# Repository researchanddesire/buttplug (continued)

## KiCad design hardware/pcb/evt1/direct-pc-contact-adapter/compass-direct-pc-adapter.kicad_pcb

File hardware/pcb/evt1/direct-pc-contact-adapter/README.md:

# Compass EVT1 direct PC contact adapter

EVT1-EA1 is a 35 × 26 × 1.6 mm four-layer external bench adapter. It connects a USB-C data port to the same four plug contacts used by the dock. The plug continues to use its native USB device interface. Connect the adapter fixture or the dock to the plug, one at a time. Routine enumeration uses the plug’s existing USB firmware.

- [KiCad project](compass-direct-pc-adapter.kicad_pro)
- [Schematic](compass-direct-pc-adapter.kicad_sch)
- [Board](compass-direct-pc-adapter.kicad_pcb)
- [Gerber and drill ZIP](quote/compass-direct-pc-adapter-gerbers.zip), [BOM](quote/compass-direct-pc-adapter-bom.csv), [placement](quote/compass-direct-pc-adapter-cpl.csv), [native checks](quote/review.json)

## Connection

J1 uses the GCT USB4105-GF-A-120 from the bench board. Each CC line has its own 5.1 kΩ pull-down. Use a native USB-C data port or powered data hub rated to supply at least 500 mA at 5 V for the first evaluation. The adapter requests default 5 V using the CC resistors and has no USB PD controller. [Bench schematic source](../one-board-dev/build_schematic.py) · [GCT drawing](https://gct.co/files/drawings/usb4105.pdf)

J2 is a top-entry JST PH B4B-PH-K(LF)(SN). Mate it with a JST PHR-4 and SPH-002T-P0.5S crimp contacts rated for the selected wire. Use a short, strain-relieved harness with equal-length D− and D+ conductors. Have the harness assembler terminate the far end on the pin board’s J94 pads. The four-pin harness is a distinct assembly. The BOM covers all 25 populated positions on the adapter PCB. [JST PH series](https://www.jst-mfg.com/product/pdf/eng/ePH.pdf) · [J94 harness source](../../../cables/evt1/dock-main/main-to-pins.yml)

| J2 to J94 | Pin signal |
| --- | --- |
| 1 to 1 | GND |
| 2 to 2 | USB D− |
| 3 to 3 | USB D+ |
| 4 to 4 | Protected 5 V |

Viewed from above with the USB connector facing the front edge, J2 pin 1 is on the right. Measured from the PCB’s front-left corner, the USB-C footprint origin is (17.5, 2.675) mm and its mating face is 1.0 mm proud. J2 pin 1 is (20.5, 21) mm and pin 4 is (14.5, 21) mm. The 2.2 mm nonplated mounting holes are at (3, 3), (32, 3), (3, 23), and (32, 23) mm. Allow wire exit above J2 and clearance for both connector tails under the board.

## Power and data

U1 limits forward contact power. The 191 kΩ, 0.5% R3 yields approximately 120–166 mA DC across the published limit equations, using a conservative ±1% resistor allowance for initial tolerance and temperature drift. The plug’s BQ24074 is strapped for USB100 with a 100 mA maximum input. The plug’s 10 kΩ and 11 kΩ branch pull-ups add up to about 1 mA at 5 V if both are pulled low. Adapter logic is supplied from J1 ahead of U1. Budget 1 mA additional upstream current for the adapter on first test and measure the actual configured and suspended current. [TPS2553-Q1 current limit](https://www.ti.com/lit/ds/symlink/tps2553-q1.pdf) · [BQ24074 USB100](https://www.ti.com/lit/ds/symlink/bq24074.pdf)

U2 is wired as an ideal diode with its CE tied to its output. It blocks sustained current from J2 towards J1. U4 senses the limiter output ahead of that reverse block. The TPS3808G09DBVR uses a 41.2 kΩ/10.0 kΩ divider. The estimated LIMIT_5V trips are 4.31 V falling and 4.35 V rising, with a 12–28 ms release delay (20 ms typical) after a valid rise. U4 and the PI3USB42 switch share the adapter 3.3 V rail. The PI3USB42 uses the A pair only and is high impedance with its supply off. Ground-referenced ESD arrays sit on both sides. The inactive pair on U5 has open pads. [LM66100 reverse blocking](https://www.ti.com/lit/ds/symlink/lm66100.pdf) · [TPS3808 timing](https://www.ti.com/lit/ds/symlink/tps3808.pdf) · [TPS7A20 capacitance](https://www.ti.com/lit/ds/symlink/tps7a20.pdf) · [PI3USB42 power-off behavior](https://www.diodes.com/datasheet/download/PI3USB42.pdf)

The threshold estimate uses TI’s nominal 4 MΩ SENSE input and 0.84 V falling threshold. Across 0–60 °C, stacking resistor initial tolerance and drift, ±1.25% threshold accuracy and 2.5% maximum hysteresis gives a rising estimate of about 4.53 V with the nominal input model. As a sensitivity check, imposing 1.7 µA at the SENSE trip gives about 4.59 V with the same corners. TI specifies that current as typical at 6.5 V. Measure both thresholds on each evaluation board under load. The more conductive divider adds approximately 0.10 mA to the switched rail at 5 V. [TPS3808 electrical characteristics and input model](https://www.ti.com/lit/ds/symlink/tps3808.pdf)

The circuit senses supply validity even with no product in the fixture. Physical contact alignment and make/break order determine what happens at the mating interface. Cold mate and disconnect the USB-C cable before swapping fixtures during initial bring-up. Keep the dock and adapter physically separate.

## First article

1. Check continuity and pin order from J2 through all four contacts before applying power. With the plug absent, sweep the input with a current-limited lab source. Capture PC_5V, LIMIT_5V, CONTACT_5V, ADAPTER_3V3 and DATA_OEn. Confirm C4 provides at least 0.47 µF effective at 3.3 V, including bias and temperature. For the room-temperature evaluation, screen for a rising trip at or below 4.55 V on LIMIT_5V and verify repeatable release under the 100 mA load. Confirm that the data switch opens below the measured falling threshold and during power removal, brownout and contact-rail overload.
2. Verify at least 4.60 V at J2 under a 100 mA static electronic load with 4.75 V at J1. Sweep the limiter through onset, confirm the DC limit on the received board, and capture momentary short current and recovery. With J1 unpowered, force 5 V at J2 pin 4 against GND from a limited supply and record J1 voltage/current. Repeat the reverse-current pulse capture with both sides on protected lab supplies.
3. Measure VBUS inrush at the host connector with the fixture already mated. J1 has 3.2 µF nominal decoupling ahead of U1 and the path after U1 adds 2 µF local plus the plug’s 4.8 µF nominal charger-input bank. The regulator output, ceramic bias, soft start, contact bounce and host current limit affect the waveform. Compare charge exceeding 100 mA against the 50 µC USB 2.0 reference in TI’s charger datasheet and capture PC and plug rails. Inspect VBUS_CHG and PGOOD at the plug to detect its diode/fuse drop and any charger input regulation. [BQ24074 inrush and input DPM](https://www.ti.com/lit/ds/symlink/bq24074.pdf)
4. With a known-good protected pack, test both USB-C cable orientations, enumeration, normal update, forced ROM recovery, charge state and detach/replug. Repeat across the intended pack states, source and cable combinations before relying on depleted-pack recovery. Capture all four contact states during partial travel on the physical fixture before live swapping. A nominal PCB or dry mating study cannot establish contact order or bounce behavior.

## Quote inputs

Request standard assembly with J1 shell stakes and J2 through-hole pins assembled at the factory. Verify the USB4105 land pattern’s 0.15 mm locating-hole clearance, J1 stake solder method and J1/J2 orientation in the assembly preview. The BOM maps all 18 order lines to vendor catalog codes. The J2 placement uses the housing center from the KiCad fabrication outline. Confirm actual stock and assembly process support in the quote. The supervisor and both divider values are a matched set. [U4 JLC catalog](https://jlcpcb.com/partdetail/TexasInstruments-TPS3808G09DBVR/C24584) · [R4 JLC catalog](https://jlcpcb.com/partdetail/257347-R0603RXX4122F10LTS/C267584) · [R5 JLC catalog](https://jlcpcb.com/partdetail/YAGEO-RT0603BRD0710KL/C95204) The pin-board wiring is covered by the separate fixture harness.

The checked Copper In1 layer is the ground reference. The connector’s USB orientation merge is carried over from the bench launch. Full-speed signal and the routed harness still require bench qualification. The source, footprint tables and routing workspace are local to this project. To rebuild, run `build_schematic.py`, export a KiCad XML netlist and run `build_pcb.py --netlist <netlist.xml> --import-ses routing.ses --finish` with KiCad 7’s bundled Python. Refill with KiCad 10 `pcb drc --refill-zones --save-board --schematic-parity <board>`. The KiCad 10 saved native board is the review and fabrication master. Run `make_quote.py --kicad-cli <path>` after a board edit to regenerate and verify exports.

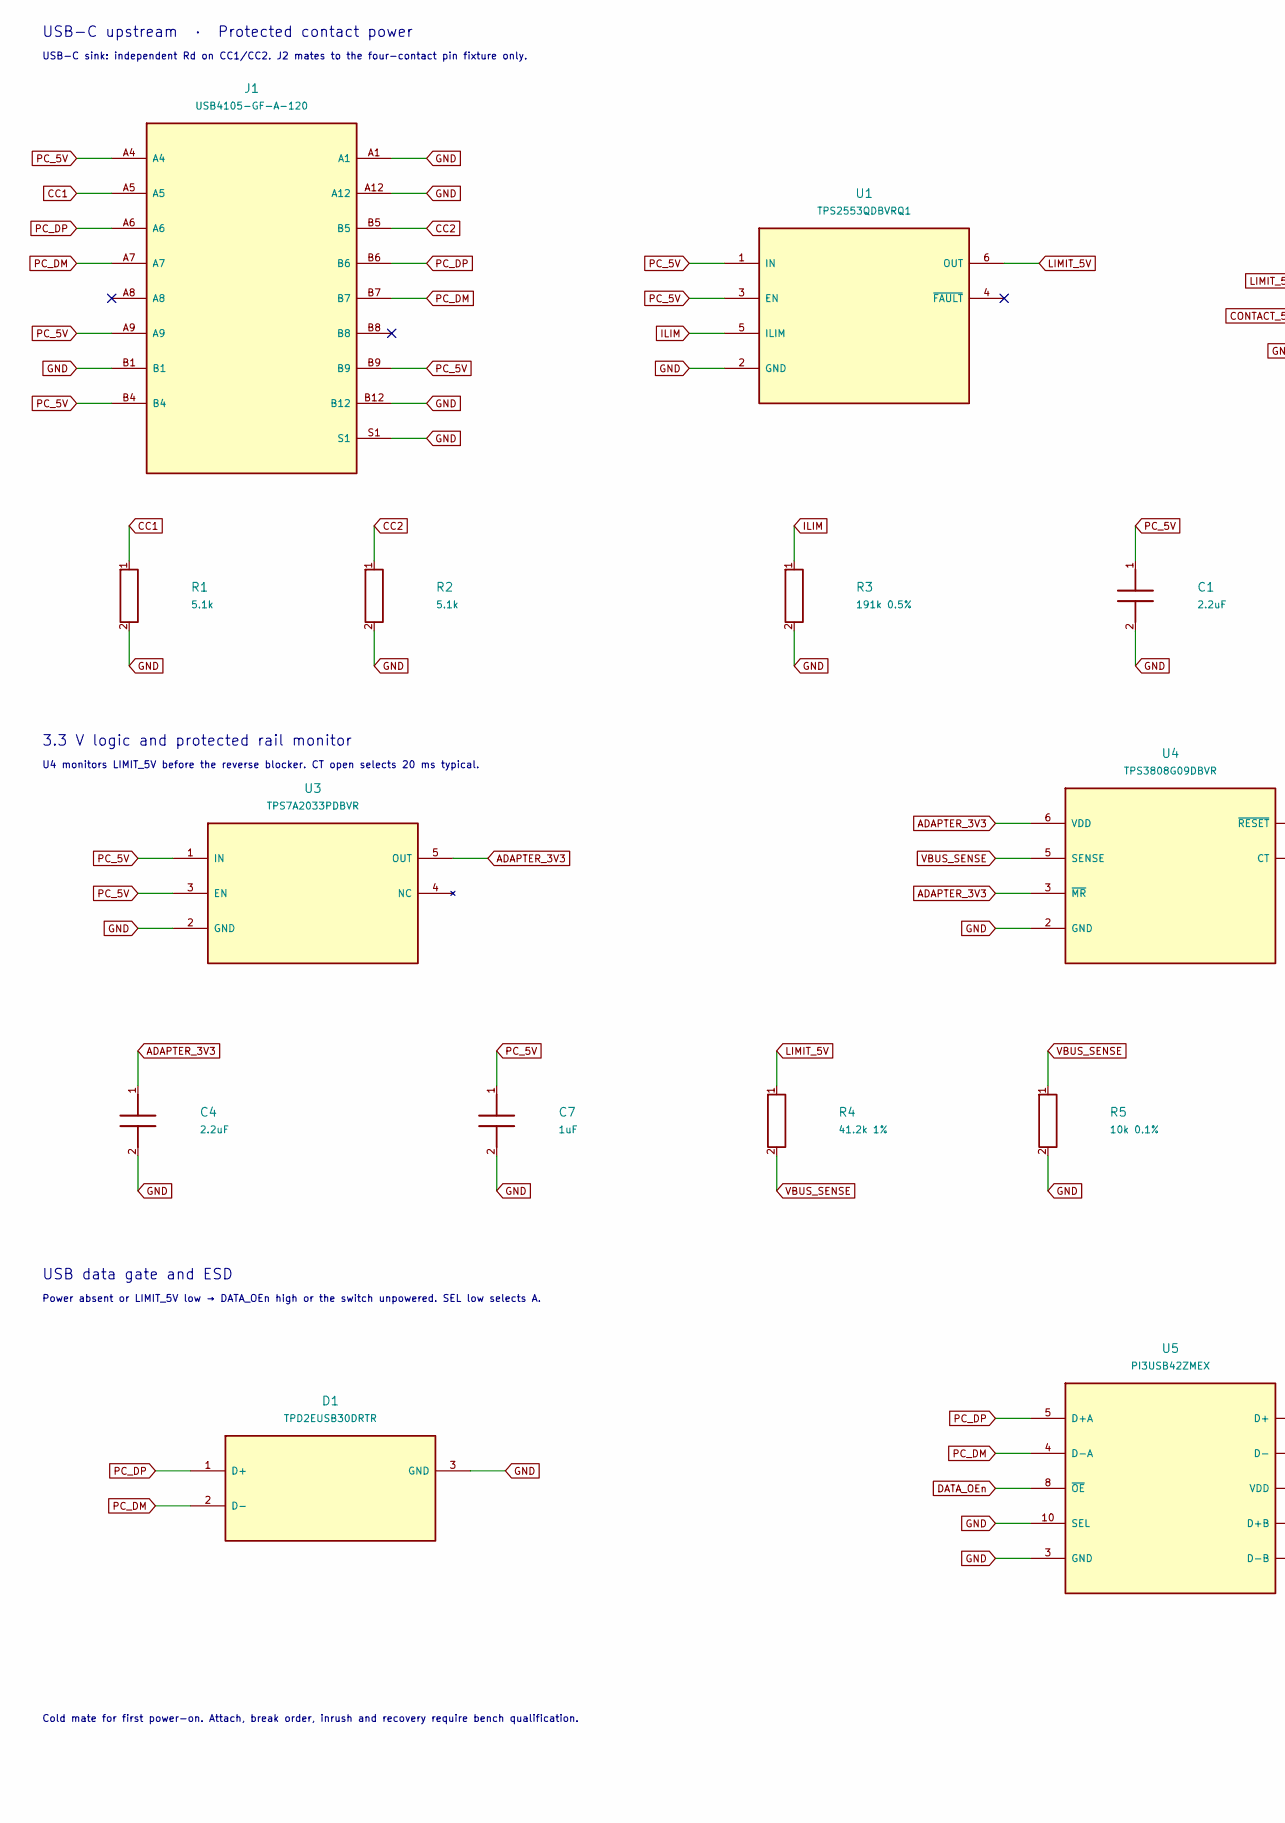
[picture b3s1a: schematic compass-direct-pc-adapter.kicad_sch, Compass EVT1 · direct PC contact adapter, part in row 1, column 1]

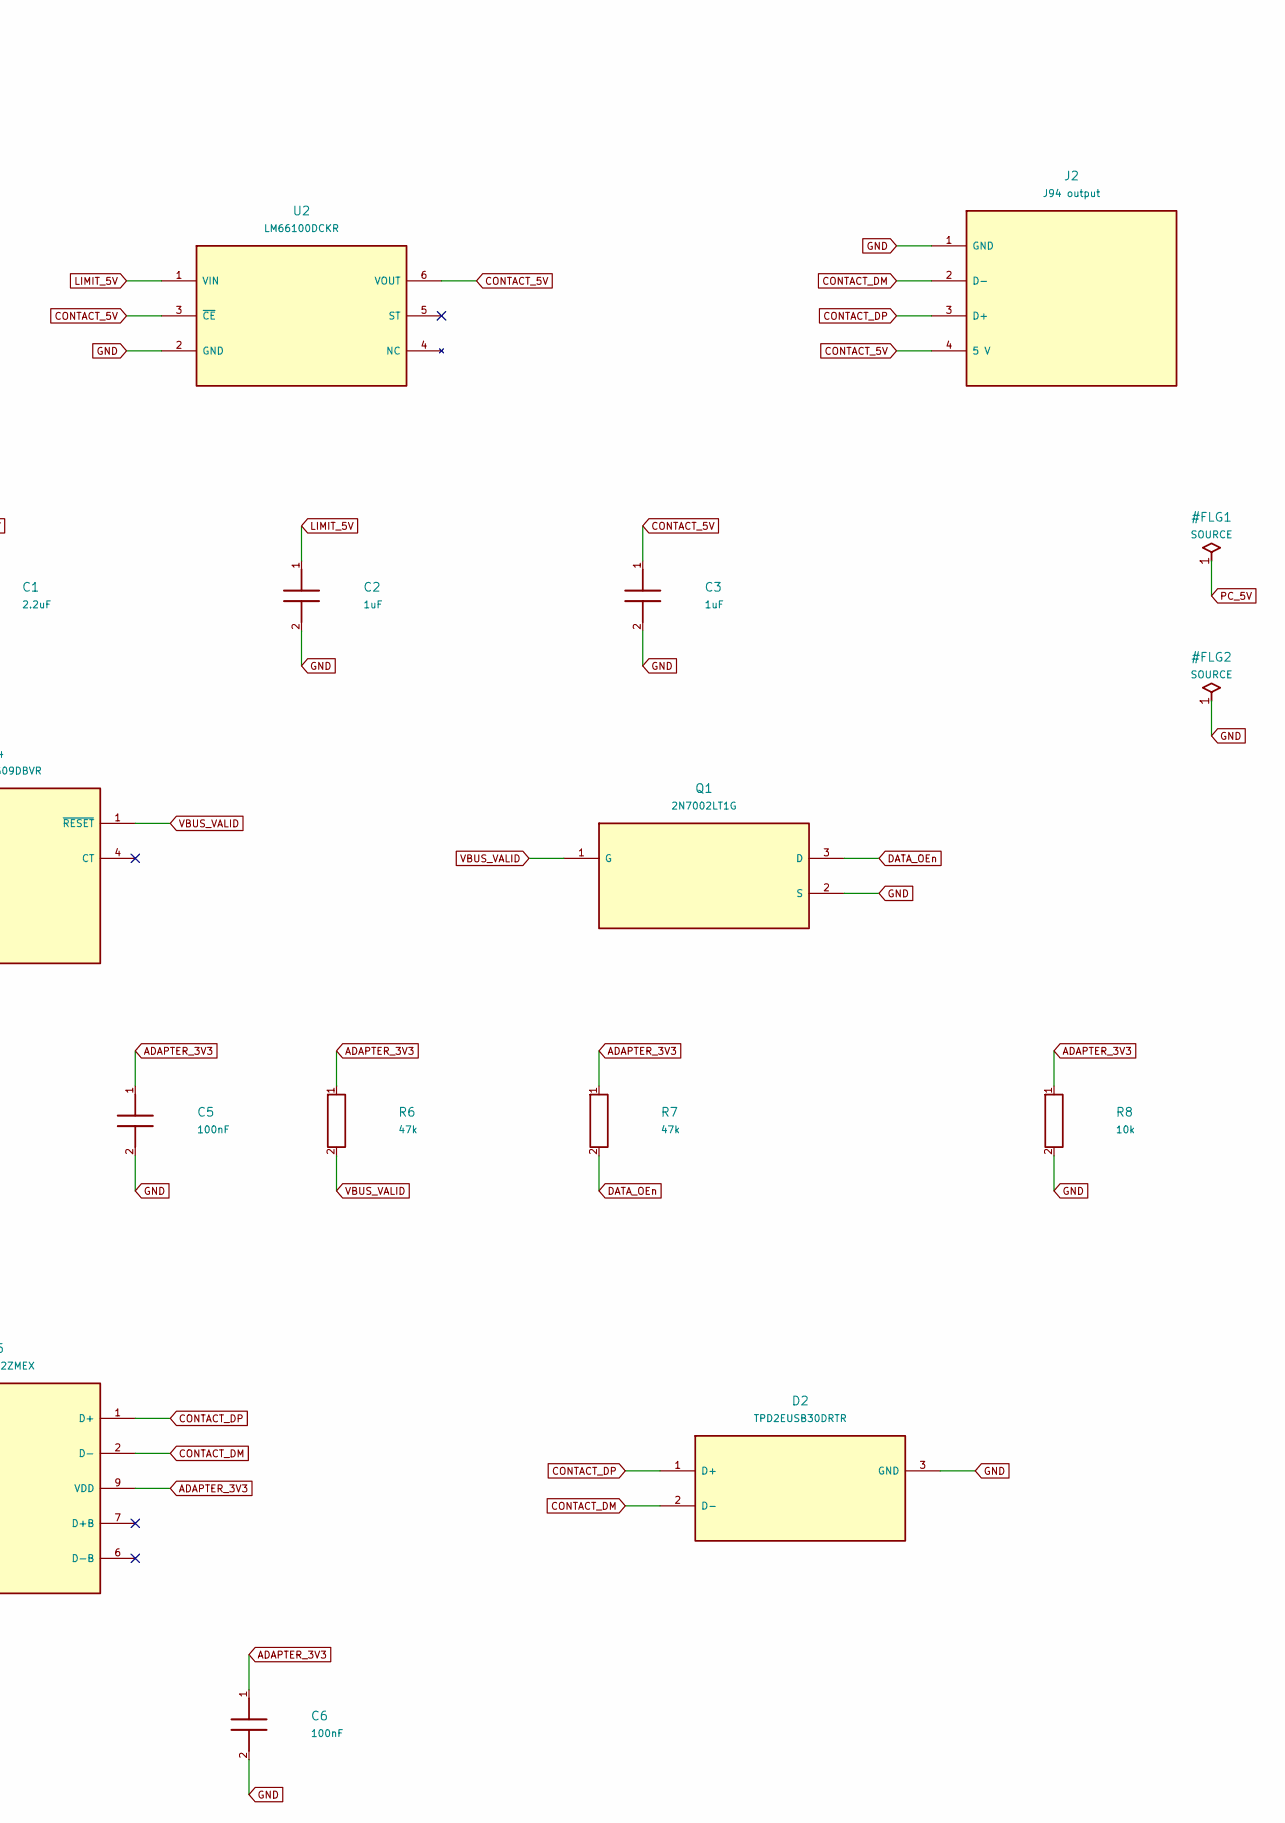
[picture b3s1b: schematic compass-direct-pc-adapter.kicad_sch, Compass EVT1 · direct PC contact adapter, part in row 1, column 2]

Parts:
C1, C4: 2.2uF; C_0603_1608Metric; MPN GRM188R71A225KE15D; LCSC C86018
C2, C3, C7: 1uF; C_0603_1608Metric; MPN GCM188R71C105KA64D; LCSC C161212
C5, C6: 100nF; C_0603_1608Metric; MPN GRM188R71H104KA93D; LCSC C77055
D1, D2: TPD2EUSB30DRTR; Texas_DRT-3; MPN TPD2EUSB30DRTR; LCSC C97502
J1: USB4105-GF-A-120; USB_C_Receptacle_GCT_USB4105-xx-A_16P_TopMnt_Horizontal; MPN USB4105-GF-A-120; LCSC C5184243
J2: J94 output; JST_PH_B4B-PH-K_1x04_P2.00mm_Vertical; MPN B4B-PH-K(LF)(SN); LCSC C265289
Q1: 2N7002LT1G; SOT-23; MPN 2N7002LT1G; LCSC C16338
R1, R2: 5.1k; R_0603_1608Metric; MPN RC0603FR-075K1L; LCSC C105580
R3: 191k 0.5%; R_0603_1608Metric; MPN RNCF0603DTC191K; LCSC C2487357
R4: 41.2k 1%; R_0603_1608Metric; MPN R0603RXX4122F10LTS; LCSC C267584
R5: 10k 0.1%; R_0603_1608Metric; MPN RT0603BRD0710KL; LCSC C95204
R6, R7: 47k; R_0603_1608Metric; MPN RC0603FR-0747KL; LCSC C105579
R8: 10k; R_0603_1608Metric; MPN RC0603FR-0710KL; LCSC C98220
U1: TPS2553QDBVRQ1; SOT-23-6; MPN TPS2553QDBVRQ1; LCSC C130055
U2: LM66100DCKR; SOT-363_SC-70-6; MPN LM66100DCKR; LCSC C2869734
U3: TPS7A2033PDBVR; SOT-23-5; MPN TPS7A2033PDBVR; LCSC C2862740
U4: TPS3808G09DBVR; SOT-23-6; MPN TPS3808G09DBVR; LCSC C24584
U5: PI3USB42ZMEX; UQFN-10_1.4x1.8mm_P0.4mm; MPN PI3USB42ZMEX; LCSC C780880

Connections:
ADAPTER_3V3: C4.1, C5.1, C6.1, R6.1, R7.1, R8.1, U3.5 (OUT), U4.3 (~MR), U4.6 (VDD), U5.9 (VDD)
CC1: J1.A5, R1.1
CC2: J1.B5, R2.1
CONTACT_5V: C3.1, J2.4 (5 V), U2.3 (~CE), U2.6 (VOUT)
CONTACT_DM: D2.2 (D-), J2.2 (D-), U5.2 (D-)
CONTACT_DP: D2.1 (D+), J2.3 (D+), U5.1 (D+)
DATA_OEn: Q1.3 (D), R7.2, U5.8 (~OE)
GND: C1.2, C2.2, C3.2, C4.2, C5.2, C6.2, C7.2, D1.3 (GND), D2.3 (GND), J1.A1, J1.A12, J1.B1, J1.B12, J1.S1, J2.1 (GND), Q1.2 (S), R1.2, R2.2, R3.2, R5.2, R8.2, U1.2 (GND), U2.2 (GND), U3.2 (GND), U4.2 (GND), U5.3 (GND), U5.10 (SEL)
ILIM: R3.1, U1.5 (ILIM)
LIMIT_5V: C2.1, R4.1, U1.6 (OUT), U2.1 (VIN)
PC_5V: C1.1, C7.1, J1.A4, J1.A9, J1.B4, J1.B9, U1.1 (IN), U1.3 (EN), U3.1 (IN), U3.3 (EN)
PC_DM: D1.2 (D-), J1.A7, J1.B7, U5.4 (D-A)
PC_DP: D1.1 (D+), J1.A6, J1.B6, U5.5 (D+A)
VBUS_SENSE: R4.2, R5.1, U4.5 (SENSE)
VBUS_VALID: Q1.1 (G), R6.2, U4.1 (~RESET)

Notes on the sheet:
USB-C upstream · Protected contact power
USB-C sink: independent Rd on CC1/CC2. J2 mates to the four-contact pin fixture only.
3.3 V logic and protected rail monitor
U4 monitors LIMIT_5V before the reverse blocker. CT open selects 20 ms typical.
USB data gate and ESD
Power absent or LIMIT_5V low → DATA_OEn high or the switch unpowered. SEL low selects A.
Cold mate for first power-on. Attach, break order, inrush and recovery require bench qualification.

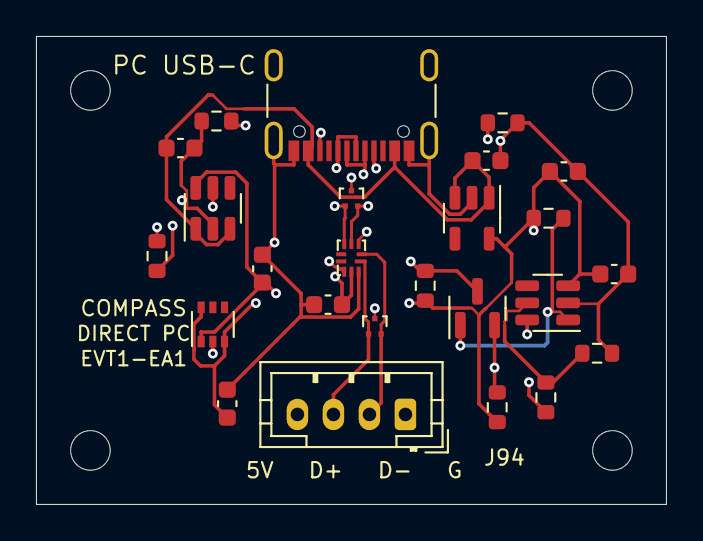
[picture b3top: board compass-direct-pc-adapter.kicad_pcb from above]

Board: 4 copper layers, 35.0 x 26.0 mm, 29 parts (0 on the bottom side), 15 nets.

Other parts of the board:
H1, H2, H3, H4: M2; MountingHole_2.2mm_M2

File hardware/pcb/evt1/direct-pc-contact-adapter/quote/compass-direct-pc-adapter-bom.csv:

Comment,Designator,Footprint,LCSC Part #,Manufacturer,MPN
2.2uF,"C1,C4",C_0603_1608Metric,C86018,Murata,GRM188R71A225KE15D
1uF,"C2,C3,C7",C_0603_1608Metric,C161212,Murata,GCM188R71C105KA64D
100nF,"C5,C6",C_0603_1608Metric,C77055,Murata,GRM188R71H104KA93D
TPD2EUSB30DRTR,"D1,D2",Texas_DRT-3,C97502,Texas Instruments,TPD2EUSB30DRTR
USB4105-GF-A-120,J1,USB_C_Receptacle_GCT_USB4105-xx-A_16P_TopMnt_Horizontal,C5184243,GCT,USB4105-GF-A-120
J94 output,J2,JST_PH_B4B-PH-K_1x04_P2.00mm_Vertical,C265289,JST,B4B-PH-K(LF)(SN)
2N7002LT1G,Q1,SOT-23,C16338,onsemi,2N7002LT1G
5.1k,"R1,R2",R_0603_1608Metric,C105580,Yageo,RC0603FR-075K1L
191k 0.5%,R3,R_0603_1608Metric,C2487357,Stackpole Electronics,RNCF0603DTC191K
41.2k 1%,R4,R_0603_1608Metric,C267584,EYANG,R0603RXX4122F10LTS
10k 0.1%,R5,R_0603_1608Metric,C95204,Yageo,RT0603BRD0710KL
47k,"R6,R7",R_0603_1608Metric,C105579,Yageo,RC0603FR-0747KL
10k,R8,R_0603_1608Metric,C98220,Yageo,RC0603FR-0710KL
TPS2553QDBVRQ1,U1,SOT-23-6,C130055,Texas Instruments,TPS2553QDBVRQ1
LM66100DCKR,U2,SOT-363_SC-70-6,C2869734,Texas Instruments,LM66100DCKR
TPS7A2033PDBVR,U3,SOT-23-5,C2862740,Texas Instruments,TPS7A2033PDBVR
TPS3808G09DBVR,U4,SOT-23-6,C24584,Texas Instruments,TPS3808G09DBVR
PI3USB42ZMEX,U5,UQFN-10_1.4x1.8mm_P0.4mm,C780880,Diodes Incorporated,PI3USB42ZMEX

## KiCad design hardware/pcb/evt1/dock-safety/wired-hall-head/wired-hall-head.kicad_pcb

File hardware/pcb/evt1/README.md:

# EVT1 electrical integration

Editable KiCad electrical revision for the current four-contact, two-wire NTC
and flange-fixed compass architecture. **The full product is not ready to
order.** All five routed PCBs pass source-bound native DRC and pad/netlist
parity. The three device boards fit the separate actual-board assembly CAD;
PCB parts are selected; non-PCB hardware, loom, factory axes and the full build package remain open. R35F boards in
`layout-seeds/` are preserved references and must not be fabricated as EVT1.

| Source | Saved state |
| --- | --- |
| `system-evt1.kicad_sch` | Full device hierarchy; native ERC passes. |
| `body/` | ADS1115 tip-NTC circuit replaces MC3635/TMP117 wiring. Charger EN1/EN2 select USB100. Routed6-layer1mm native; DRC zero. Actual component/mate envelopes fit the cap/body module. |
| `flange/` | Four targets, USB protection/22R series resistors, long-press reset and dock wake. Routed4-layer1mm native with locating tabs; DRC zero. R39 moved0.4mm to clear the tray seat; R76 moved to permit the U71 ground return. |
| `sensor/` | Routed12×10×1mm LSM303AGR board, twoØ1.6 holes on9mm centers; DRC zero. Two integral tray bosses/nonmagnetic screw envelopes register it. C83 part selected; effective capacitance and factory package axes require qualification. |
| `dock/` | Routed USB-C input board with independent CC pull-downs, USBLC6-2SC6 protection and TPS2553 current-limited power. |
| `pins/` | Routed 28×10×1mm pin board, four Mill-Max0906-2 footprints at6mm pitch. Rear wire pads at the lower edge. |
| `validation.json` | Independent native pad/netlist parity, functional pin contract and source hashes; full-product readiness remains false. |
| `native-checks.json` | Native ERC/DRC report hashes bound to exact schematics, libraries, boards, rules and exported netlists. |
| `parts-selection.json`, `pcb-ordering.csv` | Exact selections for114 purchased PCB positions/53 order lines. Eight copper-only interfaces/jumpers are assembly operations. Per-complete-device-and-dock quantities; not the human-owned product BOM. |
| `parts-validation.json` | All122 native PCB positions accounted for; independent passive MPN/case/value/rating/tolerance checks and ordering parity pass. |
| `pack-spec.json`, `PACK-RFQ.md` | BC-PACK-EVT1-001 protected-pack RFQ for the two-board EVT1:1.5A continuous,2A/100ms pulse,33×21×6.3mm maximum, two dry external NTCs. Superseded for the one-board device by `one-board/PACK-RFQ.md` (BC-PACK-EVT1-002, 3-wire pack with its own NTC and a JST SH 3P plug). |

All five PCBs pass KiCad10.0.8 DRC with zero violations/unconnected items.
Both cradle boards also pass ERC with zero errors/warnings.
The system and body schematics pass ERC. Standalone flange/sensor pages report
undriven external supplies; their supply source is included in the full system.
No ERC/DRC exclusions are used to close shorts or missing connections.

## Selected PCB parts and assembly quotes

Each board's `assembly-quote/` contains exact manufacturer part numbers,
native KiCad purchased-part positions, the saved native PCB and its matching
fabrication ZIP. The worksheets account for all122 schematic PCB positions:
114 are bought parts and eight are copper features/manual operations.
`tools/verify_evt1_parts.py` independently decodes80 passive part numbers and
checks case, nominal value, voltage/dielectric and tolerance against native
schematics. Supplier stock and acceptance are not implied.

L1/L2 select Coilcraft XFL4020-152MEC, the1.5uH family in TI's reference circuit.
Its4.3mm maximum XY envelope is included in CAD. C83 selects TDK
C2012X5R1E226M125AC,22uF/25V X5R in0805; the schematic10V marking is a minimum.
Require at least10uF effective at3.3V over the intended temperature/age before
accepting the assembled process. Nominal capacitance and a higher voltage
rating do not prove this. Effective regulator capacitance, paste/reflow,
polarized orientation and powered behavior remain commissioning checks.

Flange D1's custom footprint numbers its physical cathode as pad2; align the
stripe with the native cathode bar. Do not populate a connector on hand-solder
lands. Body JP1 stays open until charge-guard commissioning passes. The full
engineering ordering sheet does not include non-PCB hardware/loom parts.

The protected battery is specified separately for RFQ. The published EEMB
A25357 pack is rated1A continuous and is only a construction reference for the
1.5A request. CAD models the requested33×21×6.3mm maximum, two3mm×10mm NTC
head/transition envelopes and additional1.1mm thickness/0.25mm lateral growth
space. These are requested bounds, not a received/approved pack or a swelling
guarantee. Preserve six pack-module conductors and join sensor/power returns
only on the body PCB. The continuous skin is consumed/remade for EVT workshop
battery service; no rear service lid or battery path through the neck is added.
The request now uses factory28AWG power leads and a JST ACH wire-to-wire
disconnect so the battery is connected after cap threading. See the RFQ for
the two housing/contact types and factory lead datum; the CAD mated box is an
allowance. Seven current WireViz sources are in `hardware/cables/evt1/`.

Sources: [TI TPS63070](https://www.ti.com/lit/ds/symlink/tps63070.pdf),
[Coilcraft XFL4020](https://www.coilcraft.com/en-us/products/power/shielded-inductors/molded-inductor/xfl/xfl4020/),
[TDK C83](https://product.tdk.com/en/search/capacitor/ceramic/mlcc/info?part_no=C2012X5R1E226M125AC),
[EEMB cell](https://www.eemb.com/product-248),
[Vishay pack NTC](https://www.vishay.com/docs/29078/ntcle413.pdf).

Each board's `fabrication-quote/` contains Gerbers,
separate plated/nonplated Excellon drills, routed slots, ZIPs and hash manifests.
They are **quote files**, with no supplier acceptance or purchase recorded.
The archive includes a fabrication request: body6-layer/flange4-layer/sensor,
dock and pins2-layer, all1mm FR4 and ENIG. Outer copper is1oz, proposed inner
copper0.5oz. Supplier review must reconcile the actual stackup and finished
thickness; no controlled-impedance agreement is claimed. Device boards use
0.15mm tracks,0.1mm copper clearance and0.25mm hole-to-copper clearance, with
Ø0.5/0.2mm body/sensor vias andØ0.6/0.3mm flange vias. The USB4105 locating-peg land pattern
requires acceptance of0.15mm hole-to-copper clearance; routing/copper clearance
is0.2mm minimum on the cradle boards, viasØ0.6/0.3mm and edge clearance0.3mm. Do not silently substitute
a thicker pin board: its thickness sets spring compression.

The dock board has a narrow front nose so the socket reaches the case wall.
PCB local(x,y) maps to dock(X=x−54,Y=y+42,Z=5.4..6.4). The USB socket face is
X−57.5. Four M2 mounts are at local(7,3),(7,19),(25,3),(25,19).
Pin-board local(x,y) maps to dock(X=x−42,Y=8.7962,Z=50.2−y) on its front face.
P91..P94 are GND/D−/D+/5V. J94 solder lands are on **B.Cu**, at y8.5;
the revised carrier/retainer opens behind those lands. `mcad.json` is extracted
from each actual board and bound to its SHA256, not a separately guessed board.

Use the matching `evt1` firmware profile; `prototype-r0` expects different
sensors and treats GPIO10 as an input. GPIO10 is now NTC excitation.
The power switch and dock presence diode-OR into RTC GPIO1. A separate raw
power-switch net drives TPS3422's7.5s hardware reset. Mode also pulls BOOT low
through a diode, allowing ROM USB recovery without extra external contacts.
Electrical checks do not prove wake/recovery timing or successful flashing.
The two former internal reset/boot switches are removed; J4 still exposes
service EN/BOOT. External Power/Mode provide the independent recovery chord.

Sources: [TPS3422](https://www.ti.com/lit/ds/symlink/tps3422.pdf),
[ADS1115](https://www.ti.com/lit/ds/symlink/ads1115.pdf),
[LSM303AGR](https://www.st.com/resource/en/datasheet/lsm303agr.pdf),
[USB4105](https://gct.co/connector/usb4105),
[TPS2553](https://www.ti.com/lit/ds/symlink/tps2553.pdf),
[USBLC6-2](https://www.st.com/resource/en/datasheet/usblc6-2.pdf).

Rebuild with `tools/build_evt1_electrical.py` (schematics/local libraries),
`tools/build_evt1_dock_pcbs.py` (placement/offline-router exchange/MCAD data),
then native ERC/DRC and `tools/verify_evt1_electrical.py`.
The placement/router tool uses KiCad7's bundled Python; electrical/rule checks
use KiCad10.0.8. Freerouting2.0.1/Java21 was used offline with analytics disabled.
Revalidate after regeneration; the schematic builder does not synchronize PCB
layouts automatically. `tools/export_evt1_cradle.py` refuses stale validation;
`--domains body flange sensor dock pins` exports all five quote archives and
also requires current actual-board assembly checks for device boards.
Device routing work uses `tools/build_evt1_device_pcbs.py`; `placement.kicad_pcb`
files are working seeds. `place` refuses to replace a saved board unless
`--restart-layout` is explicit; preserve routing outside the output before restarting.
`preserved-control-routes.json` records source copper
for interfaces whose terminal geometry is unchanged. KiCad7 can invalidate a
live board's project settings when a second board is loaded; extract source
records as data before loading the destination. Do not use the working device
boards as a full-product fabrication release. Local repairs are recorded in
`routing-adjustments.json`. U6 zero-radius rounded pads are normalized to
rectangles in both board/library, preserving their copper geometry. J81's
GND hand-solder land intentionally includes a plated stitching via.

Run `tools/check_evt1_native.py --kicad-cli PATH` before
`tools/verify_evt1_electrical.py`; stale source/report/netlist hashes fail.
The device assembly lives in `hardware/cad/manufacturing-layout/evt1-integration/`.
Component bodies are Fab-outline/height budgets and mates are allowances,
not OEM geometry. Nominal CAD fit does not establish flexible loom access,
supplier stackups, powered operation or physical assembly.

Assembly and commissioning belong in `assembly-docs/`; the human-owned product
BOM has not been changed. Physical USB power/enumeration/suspend, thermal,
spring load, loom, sealing and complete product operation remain EVT tests.

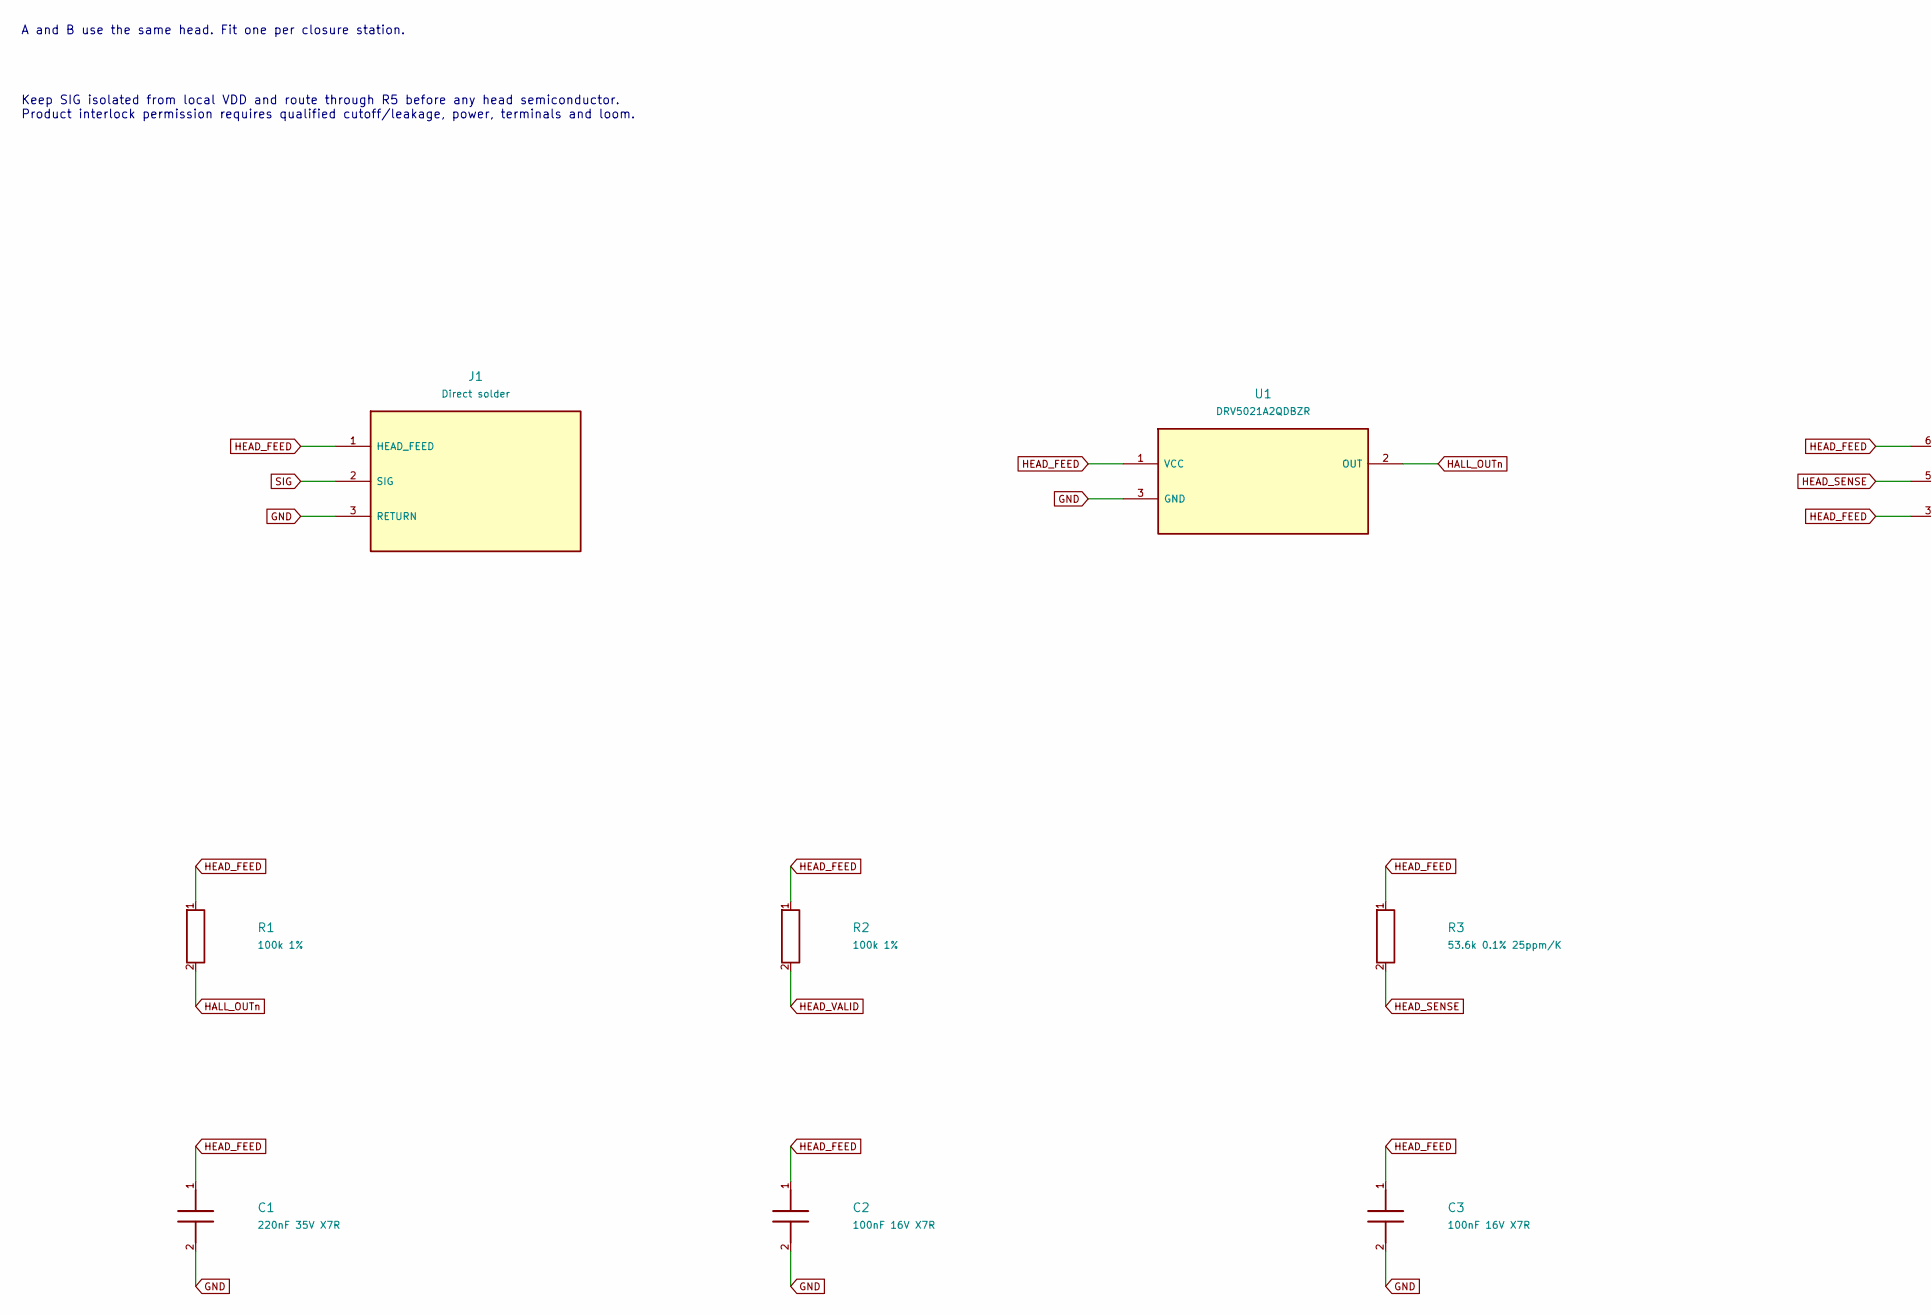
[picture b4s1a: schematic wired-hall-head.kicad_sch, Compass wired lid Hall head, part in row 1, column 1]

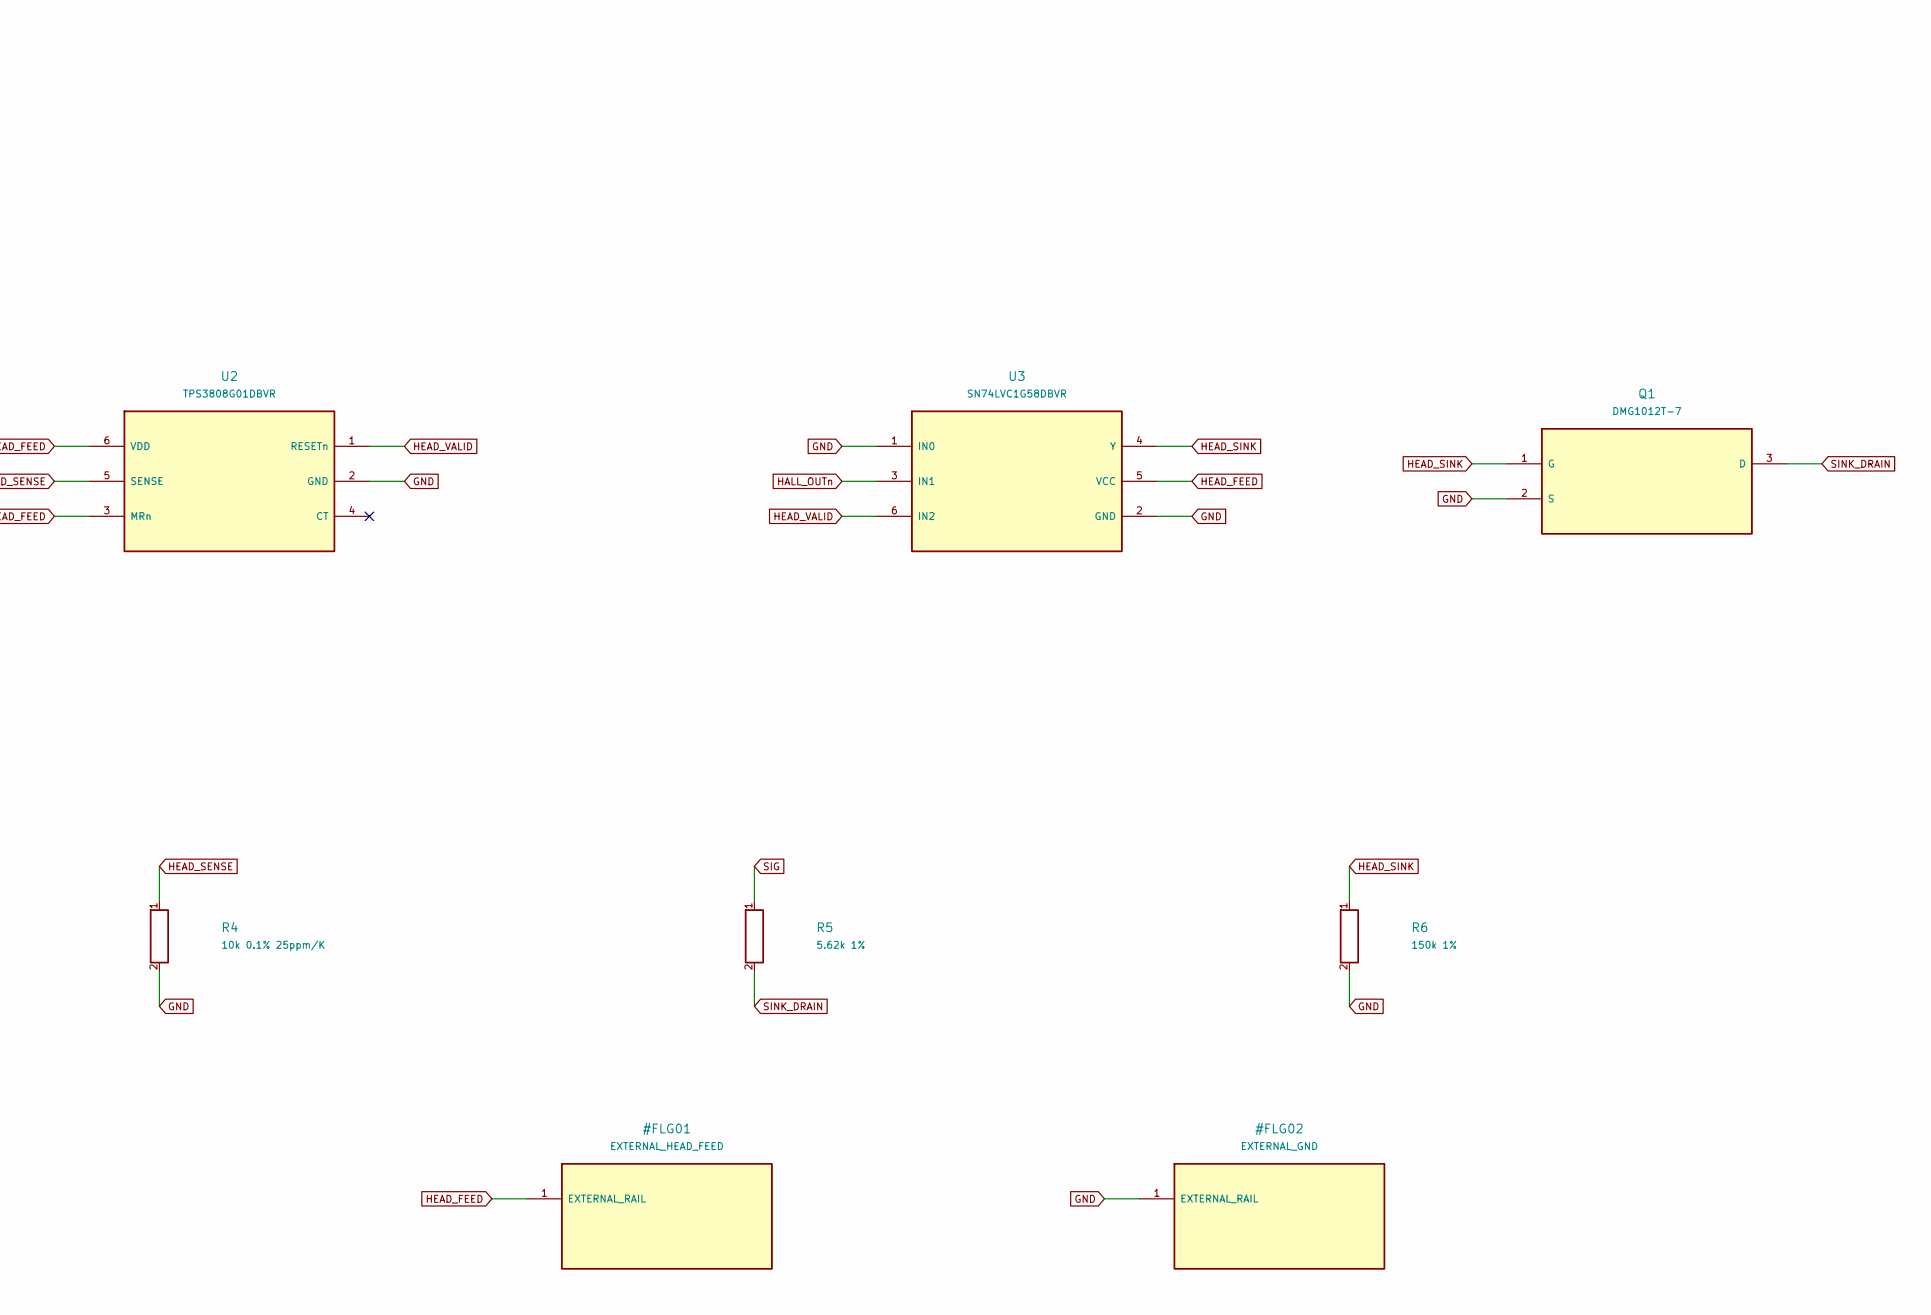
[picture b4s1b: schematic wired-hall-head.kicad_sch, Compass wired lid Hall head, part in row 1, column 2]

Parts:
C1: 220nF 35V X7R; C_0402_1005Metric; MPN C1005X7R1V224K050BC
C2, C3: 100nF 16V X7R; C_0402_1005Metric; MPN GRM155R71C104KA88D
J1: Direct solder; WirePads_3_P1.35mm; MPN WirePads_3_P1.35mm
Q1: DMG1012T-7; SOT-523; MPN DMG1012T-7
R1, R2: 100k 1%; R_0603_1608Metric; MPN RC0603FR-07100KL
R3: 53.6k 0.1% 25ppm/K; R_0603_1608Metric; MPN RT0603BRD0753K6L
R4: 10k 0.1% 25ppm/K; R_0603_1608Metric; MPN RT0603BRD0710KL
R5: 5.62k 1%; R_0603_1608Metric; MPN RC0603FR-075K62L
R6: 150k 1%; R_0603_1608Metric; MPN RC0603FR-07150KL
U1: DRV5021A2QDBZR; SOT-23; MPN DRV5021A2QDBZR
U2: TPS3808G01DBVR; SOT-23-6; MPN TPS3808G01DBVR
U3: SN74LVC1G58DBVR; SOT-23-6; MPN SN74LVC1G58DBVR

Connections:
GND: C1.2, C2.2, C3.2, J1.3 (RETURN), Q1.2 (S), R4.2, R6.2, U1.3 (GND), U2.2 (GND), U3.1 (IN0), U3.2 (GND)
HALL_OUTn: R1.2, U1.2 (OUT), U3.3 (IN1)
HEAD_FEED: C1.1, C2.1, C3.1, J1.1 (HEAD_FEED), R1.1, R2.1, R3.1, U1.1 (VCC), U2.3 (MRn), U2.6 (VDD), U3.5 (VCC)
HEAD_SENSE: R3.2, R4.1, U2.5 (SENSE)
HEAD_SINK: Q1.1 (G), R6.1, U3.4 (Y)
HEAD_VALID: R2.2, U2.1 (RESETn), U3.6 (IN2)
SIG: J1.2 (SIG), R5.1
SINK_DRAIN: Q1.3 (D), R5.2

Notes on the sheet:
A and B use the same head. Fit one per closure station.
Keep SIG isolated from local VDD and route through R5 before any head semiconductor. Product interlock permission requires qualified cutoff/leakage, power, terminals and loom.

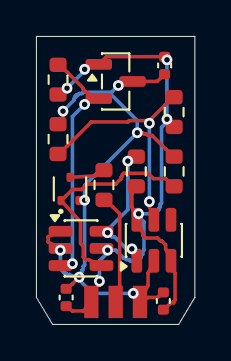
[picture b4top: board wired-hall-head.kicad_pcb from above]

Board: 2 copper layers, 8.8 x 16.0 mm, 14 parts (0 on the bottom side), 8 nets.

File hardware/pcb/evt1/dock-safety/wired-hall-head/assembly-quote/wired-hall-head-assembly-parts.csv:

Manufacturer,MPN,Quantity_per_board,Quantity_for_two_boards,References,Schematic_value,Footprint,Assembly_process,Manufacturer_source
Diodes Incorporated,DMG1012T-7,1,2,Q1,DMG1012T-7,WiredHallHead:SOT-523,SMT,https://www.diodes.com/datasheet/download/DMG1012T.pdf
Murata,GRM155R71C104KA88D,2,4,C2 C3,100nF 16V X7R,WiredHallHead:C_0402_1005Metric,SMT,https://www.murata.com/en-global/api/pdfdownloadapi?cate=luC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
TDK,C1005X7R1V224K050BC,1,2,C1,220nF 35V X7R,WiredHallHead:C_0402_1005Metric,SMT,https://product.tdk.com/en/search/capacitor/ceramic/mlcc/inf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
Texas Instruments,DRV5021A2QDBZR,1,2,U1,DRV5021A2QDBZR,WiredHallHead:SOT-23,SMT,https://www.ti.com/lit/ds/symlink/drv5021.pdf
Texas Instruments,SN74LVC1G58DBVR,1,2,U3,SN74LVC1G58DBVR,WiredHallHead:SOT-23-6,SMT,https://www.ti.com/lit/ds/symlink/sn74lvc1g58.pdf
Texas Instruments,TPS3808G01DBVR,1,2,U2,TPS3808G01DBVR,WiredHallHead:SOT-23-6,SMT,https://www.ti.com/lit/ds/symlink/tps3808.pdf
Yageo,RC0603FR-07100KL,2,4,R1 R2,100k 1%,WiredHallHead:R_0603_1608Metric,SMT,https://www.yageogroup.com/component-documentation/download/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
Yageo,RC0603FR-07150KL,1,2,R6,150k 1%,WiredHallHead:R_0603_1608Metric,SMT,https://www.yageogroup.com/component-documentation/download/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
Yageo,RC0603FR-075K62L,1,2,R5,5.62k 1%,WiredHallHead:R_0603_1608Metric,SMT,https://www.yageogroup.com/component-documentation/download/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
Yageo,RT0603BRD0710KL,1,2,R4,10k 0.1% 25ppm/K,WiredHallHead:R_0603_1608Metric,SMT,https://www.yageogroup.com/component-documentation/download/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
Yageo,RT0603BRD0753K6L,1,2,R3,53.6k 0.1% 25ppm/K,WiredHallHead:R_0603_1608Metric,SMT,https://www.yageogroup.com/component-documentation/download/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

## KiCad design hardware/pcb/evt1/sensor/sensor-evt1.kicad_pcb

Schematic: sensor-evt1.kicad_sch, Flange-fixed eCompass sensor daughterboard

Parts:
C81: 220nF; C_0402_1005Metric
C82: 100nF; C_0402_1005Metric
C83: 22uF 10V / Ceff>=10uF at3V3; C_0805_2012Metric
C84: 100nF / VDDIO local; C_0402_1005Metric
J82: TO BODY J81 / FIXED IN FLANGE; Sensor_Loom_4Land
U81: LSM303AGRTR; LGA-12_2x2mm_P0.5mm

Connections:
3V3: C82.1, C83.1, C84.1, J82.1, U81.2 (CS_XL), U81.3 (CS_MAG), U81.9 (VDD), U81.10 (VDDIO)
GND: C81.2, C82.2, C83.2, C84.2, J82.2, U81.6 (GND), U81.8 (GND)
I2C_SCL: J82.4, U81.1 (SCL)
I2C_SDA: J82.3, U81.4 (SDA)
MAG_C1: C81.1, U81.5 (C1)

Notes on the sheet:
Both sensor axes are fixed to the flange/back-arrow reference, independent of cap rotation. Place near +X flange end, away from motor, steel keepers and charging magnets. No extra pullups: existing R32/R33 pull up the common 3V3 I2C bus. Register axes to CAD. Calibrate assembled magnetic offsets; s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

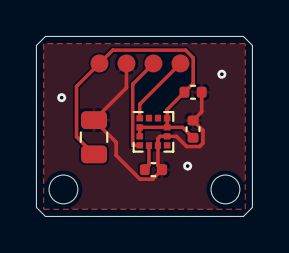
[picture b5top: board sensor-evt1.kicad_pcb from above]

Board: 2 copper layers, 12.0 x 10.0 mm, 8 parts (0 on the bottom side), 5 nets.

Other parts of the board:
H1, H2: NPTH_1.6mm_LocatingPin

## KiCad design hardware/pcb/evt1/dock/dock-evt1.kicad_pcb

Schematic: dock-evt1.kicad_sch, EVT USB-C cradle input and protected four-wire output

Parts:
C91: 1uF 10V; C_0603_1608Metric
C92: 100nF; C_0402_1005Metric
J91: USB4105-GF-A-120; USB_C_Receptacle_GCT_USB4105-xx-A_16P_TopMnt_Horizontal
J93: TO PIN BOARD J94; Contact_Loom_4Land
R91, R92: 5.1k 1%; R_0402_1005Metric
R93: 210k 1%; R_0402_1005Metric
R94: 100k; R_0402_1005Metric
TP91: FAULT TEST; TestPoint_Pad_D1.0mm
U91: USBLC6-2SC6; SOT-23-6
U92: TPS2553DBVR; SOT-23-6

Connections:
CC1: J91.A5 (CC1), R91.1
CC2: J91.B5 (CC2), R92.1
DOCK_5V: C92.1, J93.4, U92.6 (OUT)
DOCK_DM: J91.A7 (DM), J91.B7 (DM), J93.2, U91.1 (IO1_IN), U91.6 (IO1_OUT)
DOCK_DP: J91.A6 (DP), J91.B6 (DP), J93.3, U91.3 (IO2_IN), U91.4 (IO2_OUT)
DOCK_FAULT_N: R94.2, TP91.1, U92.4 (FAULT_N)
DOCK_ILIM: R93.1, U92.5 (ILIM)
GND: C91.2, C92.2, J91.A1 (GND), J91.A12 (GND), J91.B1 (GND), J91.B12 (GND), J91.S1 (SHIELD), J93.1, R91.2, R92.2, R93.2, U91.2 (GND), U92.2 (GND)
HOST_5V: C91.1, J91.A4 (VBUS), J91.A9 (VBUS), J91.B4 (VBUS), J91.B9 (VBUS), R94.1, U91.5 (VBUS), U92.1 (IN), U92.3 (EN)

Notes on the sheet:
USB2 native ESP32-C3 interface, not a USB hub. Independent 5.1k Rd on each CC. U92 limits shorts at the spring pins; reverse-voltage protection is not a substitute for keyed mating. Device charger EN1/EN2 are both low: USB100 input mode, not the former fixed500mA. Full-system current, enumeration, 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

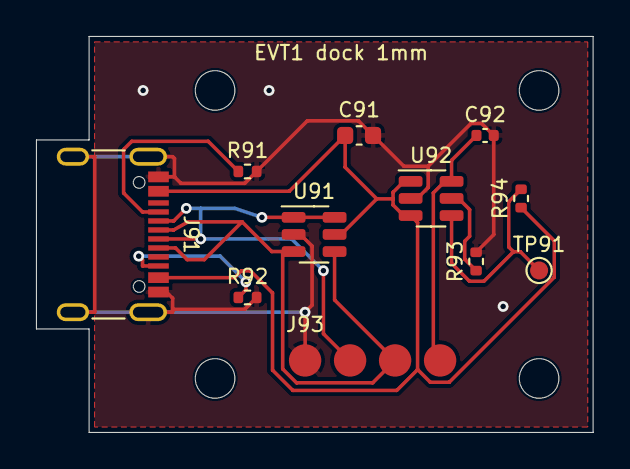
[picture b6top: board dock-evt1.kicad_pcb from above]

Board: 2 copper layers, 30.9 x 22.0 mm, 15 parts (0 on the bottom side), 9 nets.

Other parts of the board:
H1, H2, H3, H4: MountingHole_2.2mm_M2

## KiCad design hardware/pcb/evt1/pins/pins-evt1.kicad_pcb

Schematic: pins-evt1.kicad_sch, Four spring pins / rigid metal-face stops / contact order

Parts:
J94: TO USB BOARD J93; Contact_Loom_4Land
P91, P92, P93, P94: 0906-2-15-20-75-14-11-0; MillMax_0906_2

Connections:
DOCK_5V: J94.4, P94.1
DOCK_DM: J94.2, P92.1
DOCK_DP: J94.3, P93.1
GND: J94.1, P91.1

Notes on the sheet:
Board28x10x1mm. Pin centers local(4,6.7),(10,6.7),(16,6.7),(22,6.7). Local(x,y) maps to dock(X=x-42, Y=8.7962, Z=50.2-y) on component face. Tail drill0.6mm. Stops touch fixed metal target faces; silicone is not the spring-height datum. Route the short D+/D- loom as a pair. Pin fanout and loose-wire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

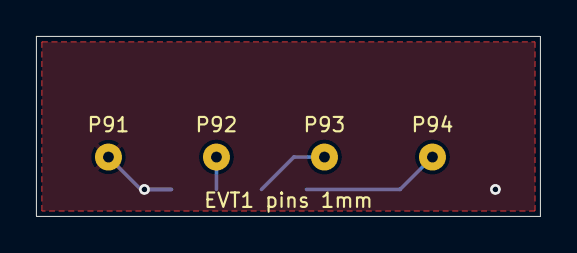
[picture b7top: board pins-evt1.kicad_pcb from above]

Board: 2 copper layers, 28.0 x 10.0 mm, 5 parts (1 on the bottom side), 4 nets.

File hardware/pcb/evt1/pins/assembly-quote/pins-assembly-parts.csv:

Manufacturer,MPN,Quantity_per_board,References,Schematic_value,Footprint,Assembly_note,Manufacturer_source
Mill-Max,0906-2-15-20-75-14-11-0,4,P91 P92 P93 P94,0906-2-15-20-75-14-11-0,EVT1:MillMax_0906_2,"Spring pin through1mm board; height/stroke are set by the carrier/retainer, not a generic component-height box.",https://www.mill-max.com/products/spring-loaded/0906
